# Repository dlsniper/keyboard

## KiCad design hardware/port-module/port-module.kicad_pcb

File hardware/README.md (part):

# hardware/

KiCad 10 projects for every board in the spec (§2a, §14). Generated by
`tools/gen_kicad.py`; checked by `tools/kicad-check.sh` (ERC + DRC on every
project, then `tools/check_interconnect.py`; reports in `build/kicad-check/`).

The generator always rewrites `lib/`, and only creates project files that are
missing, so schematic and board work is never overwritten.

## Rev 8 status (2026-09-26)

The spec moved to rev 8 (hub + dumb key modules, spec §17). **The files below are
still the rev 7 boards**, unchanged and committed as `0b22b91`; the board refactor is
the next step after the rev 8 docs are reviewed (`next.md`). Planned disposition:

| Project | Refs | Thickness | Rev 7 state | Rev 8 plan |
| --- | --- | --- | --- | --- |
| `keys-right/` `keys-left/` `keys-numpad/` | 1xx / 2xx / 3xx | 1.6 mm | empty | new design: sockets, LEDs, IS31FL3733, module controller (P19; `MSPM0G3505SPT`, link on PA0/PA1, PA18 `BSL_invoke` pull-down + rescue pad), LDO TPS7A0233PDBVR, `J_COMM` (order in spec §6, 2026-09-29), `J_DIAL` on `right` |
| `core/` | 4xx | 1.6 mm, 4 layers | schematic ERC 0; PCB 32 × 90 mm placed and routed except 7 nets (details below) | becomes **`hub-base/`**, one board (2026-09-29; the 2026-09-26 split into `hub-base/` + a vertical `hub-mcu/` board with `J_MCU` 2×30 is dropped): **MDBT50Q-U1MV2** (u.FL to the Yageo ANTX100P011B24003 PCB antenna in the case wall, 2026-10-01; the antenna needs ≥10 mm to copper, so a copper pull-back in the rear-left corner, size from M11), crystal, SWD, USB ESD, power path, TCA9548A, buttons, stacking headers; outline 94 × 77 mm (M11, front edge at y −30 behind the panel buttons); header centres chain (25, 20), slot (−5, 5), expansion (0, −20) mm from the board centre (x right from the keyboard, y to the rear), four M2 corner holes for the screws that join it to the connector layer (2026-09-29). The stock `RF_Module:Raytac_MDBT50Q` carries the antenna keepout zone, which the u.FL part does not need: whether to use a `keyboard:` copy without it is decided at capture. From `sch_core.py`: keep the power path, MCU support and expansion LDO in `sch_core.py`; drop the matrix, UART, link, module-ID and `J_ROW`/`J_COL`/`J_LED`/`J_LINK`/`J_BAT` parts; add the TCA9548A, the slot 2×16, chain 2×6 and expansion 2×10 headers (expansion pinout and CS0–CS3 with a 3V3 pull-up each per spec §6, X1), `PACK_EN`/`PACK_SENSE`, the `AUX_5V` OR input; new PCB, outline from the hub tower (M11) **Rev 8.1 (2026-09-30):** also takes the battery power path (spec §4): per pack input (`PACK_A`/`B`/`C`) SMF4L9.0CA + LM74610-Q1 + CSD17313Q2; CSD25402Q3A battery switch (TPS3840PL40 UVLO, `VDD` from the pack inputs via BAT54C + BAT54 since 2026-10-01, then 10 kΩ + 1 µF; battery sense on that node: 200 kΩ / 100 kΩ switched by a CSD25483F4 with a 470 kΩ gate pull-up and a third DMN63D8LDW half on `BAT_DIV_EN`; slide switch; DMN63D8LDW drivers; N2 pull-up 1 MΩ, Qb gate pull-up 1 MΩ, N1 pull-down 4.7 MΩ); LM74610 pump caps 1 µF; CSD25402Q3A USB switch (TPS3840PL43 on VBUS_IN; gate pull-up 10 kΩ; N4 gate delay 2.2 MΩ / 22 nF with a BAT54 bypass; VBUS_IN bleeder 100 kΩ; PL43 output also to a GPIO); `SYS` 100 µF effective; TPS630701 + XFL4020-152ME LED rail (`PS/SYNC` high, power save, 2026-10-01); TPS70933DBVR VSYS. Drops the TPS61099/MAX17222, TLV75733P, both TPS2116, TPS61023, TPS3840PH18 |
| `usb-port/` | 5xx | 1.6 mm | ERC 0 (2026-10-01) | keep as the host port board; **R502 OVLO 26.4 kΩ → 27.4 kΩ 0.1 % (E22, 2026-10-01)**: KTS1693 trip 5.38–5.78 V, under the MDBT50Q `VBUS` pad's 5.8 V abs-max |
| (new) `connector-wired/` | 12xx | 1.6 mm | — | wired connector layer carrier: slot 2×16 + chain 2×6 on top, chain pads underneath for the battery module's pogo pins, 12 Mill-Max 1578-0 gold target discs (2026-09-29, discs 2026-09-30; ESQ tails cut flush), chain/slot ESQ at the same centres as the core, 3 × `J_SLOT` (2026-09-26); slot header order in spec §6 (reversal-safe, slots 0/2 mirrored, 2026-09-29) |
| `link/` | 6xx | 1.6 mm | ERC 0, variants `upstream`/`downstream` | becomes **`comms/`** (hub population = the wired connector layer's socket boards): drop the KTS1693 population; variants `hub` (TPS22950L, `J_SLOT` 14) and `module` (BAT54C, `J_COMM` 10); VBUS TVS **TVS0500DRV** on both (was SMF6.0A; 2026-10-01, E7: stock symbol and WSON-6 footprint, land pattern checked against TI DRV0006A); CC1/CC2 in place of SBU; `J_SLOT`/`J_COMM` orders in spec §6 (2026-09-29), spares NC |
| `seam/` | 7xx | 1.2 mm | ERC 0, 4 variants | **retire** (seams are mechanical only); 7xx stays unused |
| `battery/` | 8xx | 1.6 mm | ERC 0 (rev 8 content) | **rev 8.1 (2026-09-30): becomes passive**: a 4×AA holder (MPD BC4AAPC at (−5, −15), cells along x; 2026-09-30), one PTC (Bourns MF-MSMF125/16X), the chain line shift (own pack → `PACK_A`; `PACK_A`/`PACK_B` from the discs → `PACK_B`/`PACK_C`; `PACK_C` ends), **pogo parts**: Samtec DW-06-17-T-D-254 riser at (25, 20) through a 1.6 mm cap board carrying the Mill-Max 827-22-012-10-004101 strip at (25, 28), 12 Mill-Max 1578-0 discs on ENIG pads underneath at (25, 28) (spec §4). The rev 7 pack chain, LM66200 and BAT54 leave the module (to the hub or dropped). The cap board is a small extra PCB per module |
| `dial/` | 9xx | 1.6 mm | ERC 0, PCB DRC + parity 0 | keep; recheck the A/B filter against the module controller (P19) |
| `expansion/` | 10xx | 1.6 mm | ERC 0 | keep, on the hub |
| `plate/plate-*` | none | 1.5 mm | outlines pending | keep |
| `common/` | — | — | empty sheets (LED matrix, link routing) | keep the LED matrix sheet; replace link routing with a module-controller block |

`tools/check_interconnect.py` needs its `MATES`/`PENDING` tables rebuilt for rev 8
(`J_SLOT`↔hub, `J_COMM`↔key boards, `J_CHAIN`).

## Projects (rev 7 detail, still describing the files on disk)

| Project | Refs | Thickness | Notes |
| --- | --- | --- | --- |
| `keys-right/` | 1xx | 1.6 mm | |
| `keys-left/` | 2xx | 1.6 mm | |
| `keys-numpad/` | 3xx | 1.6 mm | |
| `core/` | 4xx | 1.6 mm | **4 copper layers**, outline **32 × 90 mm** at (100, 100), placed 2026-09-16 (dielectric split is a placeholder until the fab stackup is chosen); antenna rule areas + net classes `VBUS_HI`/`POWER`/`USB` 2026-09-16; autorouted (Freerouting) 2026-09-16; rip-up 2026-09-24 (LED_BOOST hops to B.Cu at U410, R434 rotated 180°): 7 real + 8 on-purpose unconnected; `core.kicad_dru` U401 escape rule (0.127 mm inside `U401_ESCAPE`) 2026-09-25 |
| `usb-port/` | 5xx | 1.6 mm | min drill 0.15 mm (KTS1693 WLCSP) |
| `link/` | 6xx | 1.6 mm | min drill 0.15 mm (KTS1693 WLCSP) |
| `seam/` | 7xx | **1.2 mm** | SAMZO spring-half tails are 1.50 mm |
| `battery/` | 8xx | 1.6 mm | |
| `dial/` | 9xx | 1.6 mm | |
| `expansion/` | 10xx | 1.6 mm | 1xx–9xx were taken (2026-09-15) |
| `plate/plate-*` | none | 1.5 mm | FR4, no copper |

The core, battery, USB port, link, seam, dial and expansion schematics are written by `tools/sch_core.py`, `tools/sch_battery.py`,
`tools/sch_usb_port.py`, `tools/sch_link.py`, `tools/sch_seam.py`, `tools/sch_dial.py` and `tools/sch_expansion.py` (shared code in `tools/schlib.py`, kicad-sch-api in `.venv/`),
which refuse to overwrite a sheet that already has symbols unless run with `--force`,
and fail if KiCad's exported netlist differs from the nets they intended. Symbol UUIDs
are `uuid5("keyboard/<board>/<ref>")` (2026-09-15), so a `--force` rerun keeps PCB
footprints linked to their symbols. Mounting holes are schematic symbols
(`Mechanical:MountingHole`, not in BOM), so PCB schematic-parity reports nothing board-only.

`tools/check_interconnect.py` (2026-09-16) audits every JST GH header from the scripts'
`PARTS` tables: mated headers agree pin for pin through a per-pair net alias table
(`MATES`), with the same MPN; end-reversed, a power pin only faces its own net, and GND
facing a signal needs a `GND_SIGNAL_OK` reason; power nets have ≥2 contacts; pin counts
are unique per header type. Headers whose mate is on a keys-* board are listed in
`PENDING` until those schematics exist; an unlisted header is an error.

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
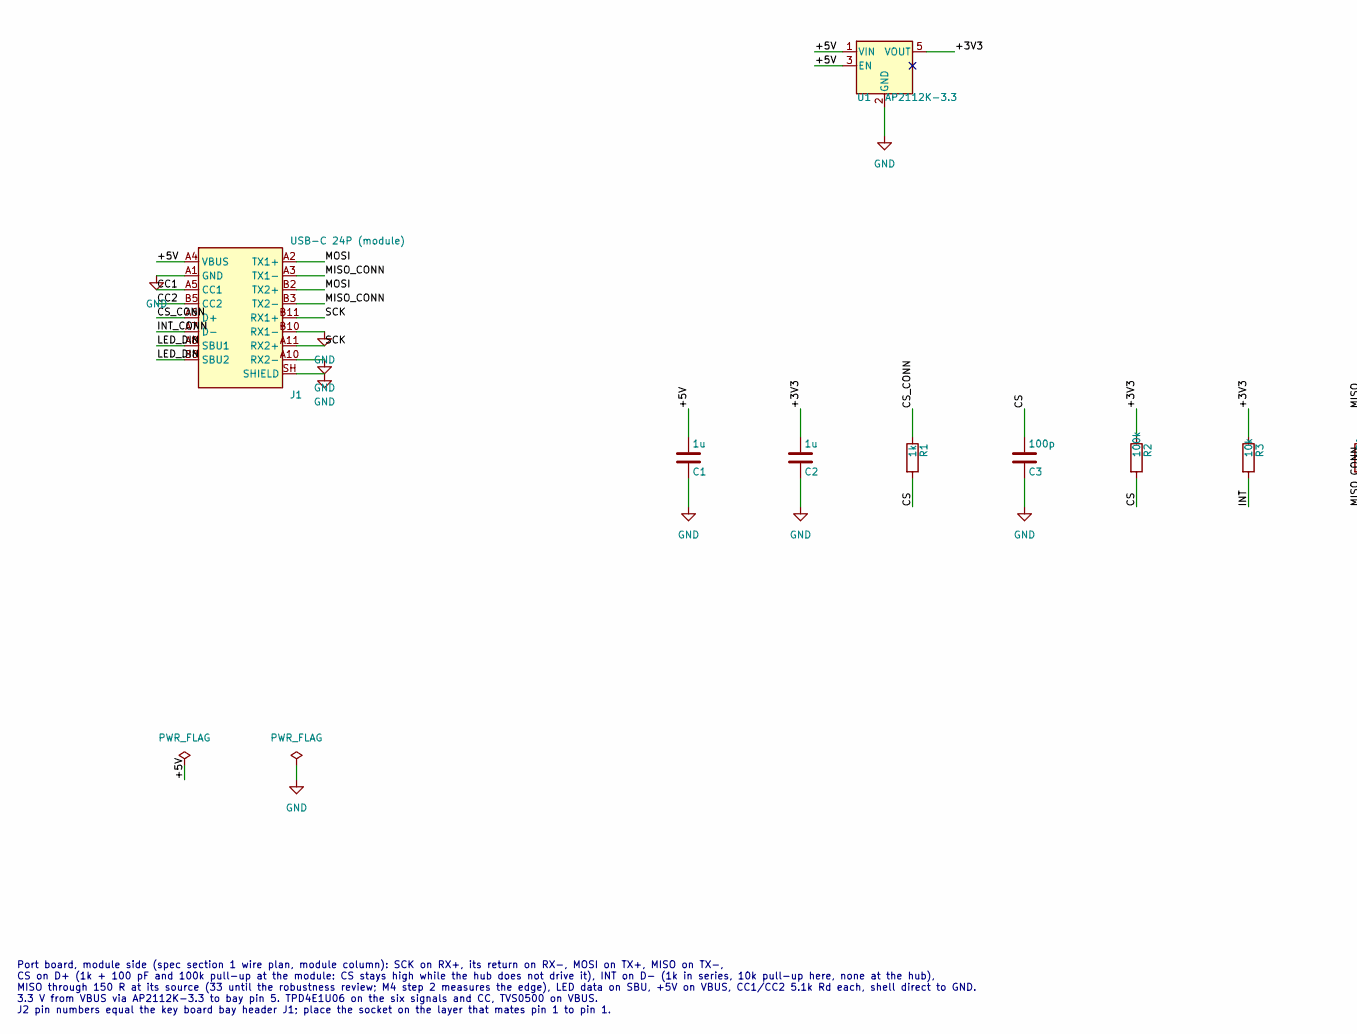
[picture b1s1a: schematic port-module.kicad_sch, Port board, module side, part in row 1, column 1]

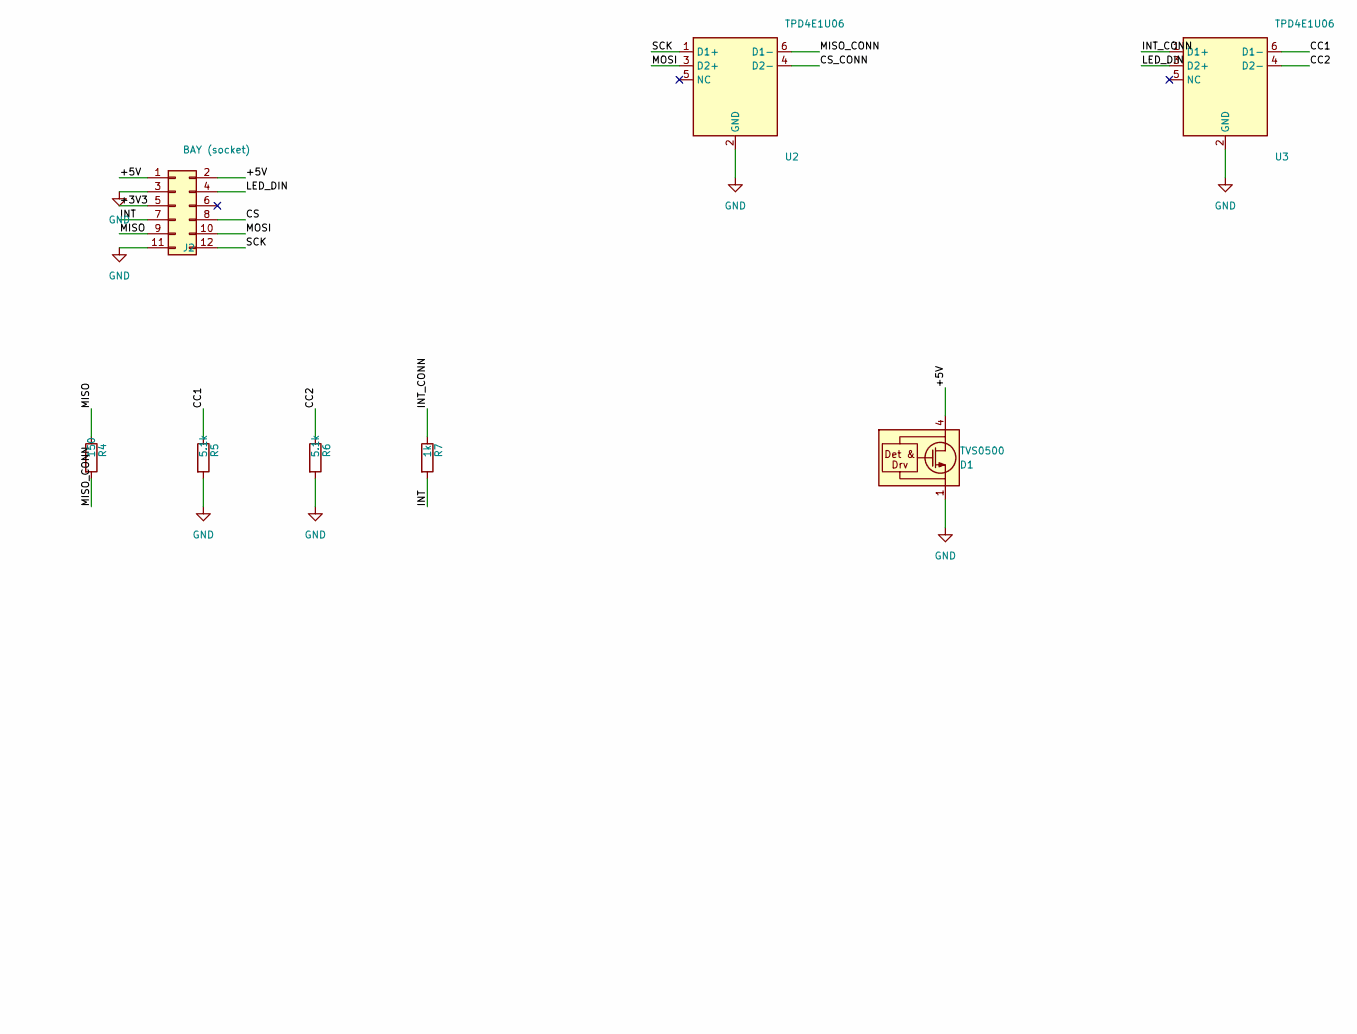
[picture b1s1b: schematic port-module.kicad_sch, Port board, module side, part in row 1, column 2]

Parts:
C1, C2: 1u; C_0805_2012Metric_Pad1.18x1.45mm_HandSolder; Voltage 16V
C3: 100p; C_0805_2012Metric_Pad1.18x1.45mm_HandSolder; Voltage 50V
D1: TVS0500; WSON-6-1EP_2x2mm_P0.65mm_EP1x1.6mm; MPN TI TVS0500DRVR
J1: USB-C 24P (module); USB_C_Receptacle_Amphenol_12401548E4-2A; MPN Amphenol 12401548E4-2A (24-pin, horizon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
J2: BAY (socket); PinSocket_2x06_P2.54mm_Vertical; MPN generic 2x6 2.54 mm socket
R1, R7: 1k; R_0805_2012Metric_Pad1.20x1.40mm_HandSolder; Tolerance 1%
R2: 100k; R_0805_2012Metric_Pad1.20x1.40mm_HandSolder; Tolerance 1%
R3: 10k; R_0805_2012Metric_Pad1.20x1.40mm_HandSolder; Tolerance 1%
R4: 150; R_0805_2012Metric_Pad1.20x1.40mm_HandSolder; Tolerance 1%
R5, R6: 5.1k; R_0805_2012Metric_Pad1.20x1.40mm_HandSolder; Tolerance 1%
U1: AP2112K-3.3; SOT-23-5; MPN Diodes Inc AP2112K-3.3TRG1
U2, U3: TPD4E1U06; TI_SOT-23-6_DBV0006A; MPN TI TPD4E1U06DBVR

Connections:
/+3V3: C2.1, J2.5, R2.1, R3.1, U1.5 (VOUT)
/+5V: C1.1, D1.4 (IN), D1.5 (IN), D1.6 (IN), J1.A4 (VBUS), J1.A9 (VBUS), J1.B4 (VBUS), J1.B9 (VBUS), J2.1, J2.2, U1.1 (VIN), U1.3 (EN)
/CC1: J1.A5 (CC1), R5.1, U3.6 (D1-)
/CC2: J1.B5 (CC2), R6.1, U3.4 (D2-)
/CS: C3.1, J2.8, R1.2, R2.2
/CS_CONN: J1.A6 (D+), J1.B6 (D+), R1.1, U2.4 (D2-)
/INT: J2.7, R3.2, R7.2
/INT_CONN: J1.A7 (D-), J1.B7 (D-), R7.1, U3.1 (D1+)
/LED_DIN: J1.A8 (SBU1), J1.B8 (SBU2), J2.4, U3.3 (D2+)
/MISO: J2.9, R4.1
/MISO_CONN: J1.A3 (TX1-), J1.B3 (TX2-), R4.2, U2.6 (D1-)
/MOSI: J1.A2 (TX1+), J1.B2 (TX2+), J2.10, U2.3 (D2+)
/SCK: J1.A11 (RX2+), J1.B11 (RX1+), J2.12, U2.1 (D1+)
GND: C1.2, C2.2, C3.2, D1.1 (GND), D1.2 (GND), D1.3 (GND), D1.7 (GND), J1.A1 (GND), J1.A10 (RX2-), J1.A12 (GND), J1.B1 (GND), J1.B10 (RX1-), J1.B12 (GND), J1.SH (SHIELD), J2.3, J2.11, R5.2, R6.2, U1.2 (GND), U2.2 (GND), U3.2 (GND)

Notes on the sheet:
Port board, module side (spec section 1 wire plan, module column): SCK on RX+, its return on RX-, MOSI on TX+, MISO on TX-, CS on D+ (1k + 100 pF and 100k pull-up at the module: CS stays high while the hub does not drive it), INT on D- (1k in series, 10k pull-up here, none at the hub), MISO through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

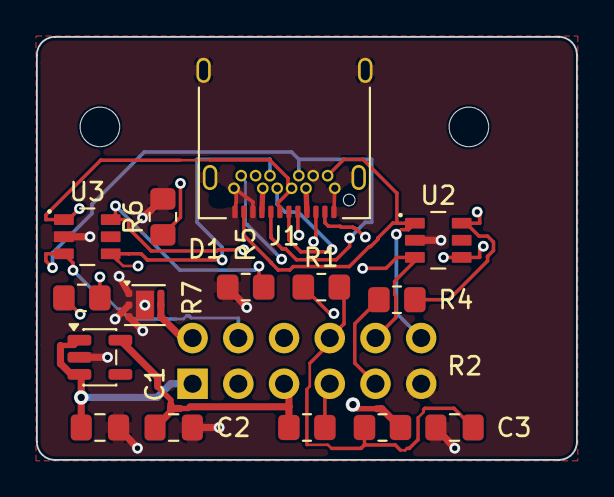
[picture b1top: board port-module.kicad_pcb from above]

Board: 4 copper layers, 30.0 x 23.5 mm, 18 parts (1 on the bottom side), 14 nets.

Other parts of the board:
H1, H2: MountingHole_2.2mm_M2

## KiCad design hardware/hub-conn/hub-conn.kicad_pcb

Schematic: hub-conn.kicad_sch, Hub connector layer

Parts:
C1, C5, C7, C9, C11, C13, C15, C26, C28, C34, C36, C37, C38, C46: 100n; C_0805_2012Metric_Pad1.18x1.45mm_HandSolder; Voltage 16V
C2, C3: 10n; C_0805_2012Metric_Pad1.18x1.45mm_HandSolder; Voltage 16V
C4, C6, C8, C10, C12, C14, C33: 10u; C_0805_2012Metric_Pad1.18x1.45mm_HandSolder; Voltage 16V
C16, C17, C18, C19, C20, C21, C22, C23, C24, C25: 1u; C_0805_2012Metric_Pad1.18x1.45mm_HandSolder; Voltage 16V
C27: 22n; C_0805_2012Metric_Pad1.18x1.45mm_HandSolder; Voltage 16V
C29, C30, C31, C32: 47u; C_1210_3225Metric_Pad1.33x2.70mm_HandSolder; Voltage 16V
C35, C47: 220u; CP_Elec_8x10; Voltage 16V; MPN 220 uF 16 V aluminium polymer, ESR 30 m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
C39, C43, C44, C45: 22u; C_1210_3225Metric_Pad1.33x2.70mm_HandSolder; Voltage 16V
C40: 1u; C_0603_1608Metric; Voltage 16V
C41: 15n; C_0805_2012Metric_Pad1.18x1.45mm_HandSolder; Voltage 16V
C42: 470p; C_0805_2012Metric_Pad1.18x1.45mm_HandSolder; Voltage 16V
D1, D2, D3: TVS0500; WSON-6-1EP_2x2mm_P0.65mm_EP1x1.6mm; MPN TI TVS0500DRVR
D4, D7, D10, D13, D15: SMF4L9.0CA; D_SOD-123FL_Littelfuse; MPN Littelfuse SMF4L9.0CA
D5, D8, D11, D14, D17, D18: BAT54C; SOT-23; MPN Diodes BAT54C-7-F
D6, D9, D12, D16, D19, D20: BAT54; SOT-23; MPN Diodes BAT54-7-F
D21: DNP (Qi); D_SOD-123F; MPN not fitted: Schottky SOD-123F, 20 V, ch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; not fitted
F1: DNP (Qi); Fuse_1206_3216Metric; MPN not fitted: chip fuse 1206, chosen with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; not fitted
J1: STACK (ESQ, socket up); PinSocket_2x25_P2.54mm_Vertical; MPN Samtec ESQ-125-24-T-D (stack-through: b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
J2: J_USB (host port board); JST_GH_SM11B-GHS-TB_1x11-1MP_P1.25mm_Horizontal; MPN JST SM11B-GHS-TB
J3: CHAIN (to AA module 1); PogoTarget_2x08_P2.54mm; MPN 16 x Mill-Max 1578-0-57-15-00-00-03-0 t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
J4: MODULE PORT A; USB_C_Receptacle_Amphenol_12401548E4-2A; MPN Amphenol 12401548E4-2A (24-pin, horizon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
J5: MODULE PORT B; USB_C_Receptacle_Amphenol_12401548E4-2A; MPN Amphenol 12401548E4-2A (24-pin, horizon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
J6: MODULE PORT C; USB_C_Receptacle_Amphenol_12401548E4-2A; MPN Amphenol 12401548E4-2A (24-pin, horizon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
L1: 4.7u; L_Coilcraft_XAL7070-XXX; MPN Coilcraft XAL7070-472ME (Isat 15 A, 14.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
Q1, Q4, Q7, Q10, Q13: SQ4184EY; SOIC-8_3.9x4.9mm_P1.27mm; MPN Vishay SQ4184EY-T1_GE3
Q2, Q5, Q8, Q11, Q18, Q20: CSD25402Q3A; VSON-8_3.3x3.3mm_P0.65mm_NexFET; MPN TI CSD25402Q3A
Q3, Q6, Q9, Q12, Q14, Q15, Q17, Q19, Q21: DMN63D8LDW; SOT-363_SC-70-6; MPN Diodes DMN63D8LDW-7
Q16: CSD25483F4; TI_PicoStar-3_1.0x0.6mm_YJC0003A; MPN TI CSD25483F4
R1, R13, R15, R16, R26, R28, R29, R39, R41, R42, R70, R81, R86: 10k; R_0805_2012Metric_Pad1.20x1.40mm_HandSolder; Tolerance 1%
R2, R3, R5, R6, R10, R11, R12, R17, R19, R23, R24, R25, R30, R32, R36, R37, R38, R43, R45, R49, R55, R61, R67, R73, R74, R80, R83, R88: 100k; R_0805_2012Metric_Pad1.20x1.40mm_HandSolder; Tolerance 1%
R4: 0R; R_0805_2012Metric_Pad1.20x1.40mm_HandSolder; Tolerance 1%; not fitted
R7, R8, R9, R20, R21, R22, R33, R34, R35: 33; R_0805_2012Metric_Pad1.20x1.40mm_HandSolder; Tolerance 1%
R14, R27, R40, R78: 1k; R_0805_2012Metric_Pad1.20x1.40mm_HandSolder; Tolerance 1%
R18, R31, R44: 330; R_0805_2012Metric_Pad1.20x1.40mm_HandSolder; Tolerance 1%
R46, R52, R58, R64, R75, R77: 1M; R_0805_2012Metric_Pad1.20x1.40mm_HandSolder; Tolerance 1%
R47, R53, R59, R65, R79: 2.2M; R_0805_2012Metric_Pad1.20x1.40mm_HandSolder; Tolerance 1%
R48, R54, R60, R66, R76: 4.7M; R_0805_2012Metric_Pad1.20x1.40mm_HandSolder; Tolerance 1%
R50, R56, R62, R68: 910k; R_0805_2012Metric_Pad1.20x1.40mm_HandSolder; Tolerance 1%
R51, R57, R63, R69: 22k; R_0805_2012Metric_Pad1.20x1.40mm_HandSolder; Tolerance 1%
R71: 470k; R_0805_2012Metric_Pad1.20x1.40mm_HandSolder; Tolerance 1%
R72: 200k; R_0805_2012Metric_Pad1.20x1.40mm_HandSolder; Tolerance 1%
R82: 15k; R_0805_2012Metric_Pad1.20x1.40mm_HandSolder; Tolerance 1%
R84: 54.9k; R_0805_2012Metric_Pad1.20x1.40mm_HandSolder; Tolerance 1%
R85: 133k; R_0805_2012Metric_Pad1.20x1.40mm_HandSolder; Tolerance 1%
R87: 49.9k; R_0805_2012Metric_Pad1.20x1.40mm_HandSolder; Tolerance 1%
R89: 31.6k; R_0805_2012Metric_Pad1.20x1.40mm_HandSolder; Tolerance 1%
R90: 12k; R_0805_2012Metric_Pad1.20x1.40mm_HandSolder; Tolerance 1%
U1: 74AHCT125; SOIC-14_3.9x8.7mm_P1.27mm; MPN 74AHCT125, SOIC-14
U2, U6, U10: TPS25810; Texas_RVC0020A_WQFN-20-1EP_3x4mm_P0.5mm_EP1.6x2.6mm; MPN TI TPS25810RVCR
U3, U7, U11: 74LVC125A; SOIC-14_3.9x8.7mm_P1.27mm; MPN 74LVC125A, SOIC-14
U4, U5, U8, U9, U12, U13: TPD4E1U06; TI_SOT-23-6_DBV0006A; MPN TI TPD4E1U06DBVR
U14, U16, U18, U20, U21: LM74610-Q1; VSSOP-8_3x3mm_P0.65mm; MPN TI LM74610QDGKRQ1
U15, U17, U19, U22: TPS3840PL43; TI_SOT-23-5_DBV0005A; MPN TI TPS3840PL43DBVR
U23: TPS3840PL40; TI_SOT-23-5_DBV0005A; MPN TI TPS3840PL40DBVR
U24: TPS3840PL36; TI_SOT-23-5_DBV0005A; MPN TI TPS3840PL36DBVR
U25: TPS552892; TI_VQFN-HR-21_5x3mm_RYQ0021A; MPN TI TPS552892RYQR
U26: TPS3700; TSOT-23-6; MPN TI TPS3700DDCR

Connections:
/+3V3: C7.1, C11.1, C15.1, J1.5, J1.6, Q14.2 (G1), Q14.5 (G2), Q15.2 (G1), Q15.5 (G2), R1.1, R2.1, R13.1, R15.1, R26.1, R28.1, R39.1, R41.1, U3.14 (VCC), U7.14 (VCC), U11.14 (VCC)
/+5V: C1.1, C4.1, C5.1, C8.1, C9.1, C12.1, C13.1, C43.1, C44.1, C45.1, C46.1, C47.1, J1.1, J1.2, R3.1, R85.1, R88.1, U1.13 (~4OE), U1.14 (VCC), U2.2 (IN1), U2.3 (IN1), U2.4 (IN2), U2.5 (AUX), U2.7 (CHG), U6.2 (IN1), U6.3 (IN1), U6.4 (IN2), U6.5 (AUX), U6.7 (CHG), U10.2 (IN1), U10.3 (IN1), U10.4 (IN2), U10.5 (AUX), U10.7 (CHG), U25.11 (VOUT), U25.12 (ISP), U25.13 (ISN)
/AUX_5V: F1.1, J3.8, J3.9
/AUX_F: D21.2 (A), F1.2
/BAT_DIV_EN: J1.39, Q17.2 (G1), R74.1
/BLD2: Q14.6 (D1), R51.2
/BLD3: Q14.3 (D2), R57.2
/BLD4: Q15.6 (D1), R63.2
/BLD5: Q15.3 (D2), R69.2
/BLK1: D14.3, Q12.2 (G1), R66.1
/BLK2: D5.3, D14.2, Q3.2 (G1), R48.1
/BLK3: D5.2, D8.3, Q6.2 (G1), R54.1
/BLK4: D8.2, D11.3, Q9.2 (G1), R60.1
/BOOT1: C37.1, U25.20 (BOOT1)
/BOOT2: C38.1, U25.19 (BOOT2)
/CC1: J2.3, R5.1
/CC1_A: J4.A5 (CC1), U2.11 (CC1), U5.6 (D1-)
/CC1_B: J5.A5 (CC1), U6.11 (CC1), U9.6 (D1-)
/CC1_C: J6.A5 (CC1), U10.11 (CC1), U13.6 (D1-)
/CC1_SENSE: C2.1, J1.35, R5.2
/CC2: J2.9, R6.1
/CC2_A: J4.B5 (CC2), U2.13 (CC2), U5.4 (D2-)
/CC2_B: J5.B5 (CC2), U6.13 (CC2), U9.4 (D2-)
/CC2_C: J6.B5 (CC2), U10.13 (CC2), U13.4 (D2-)
/CC2_SENSE: C3.1, J1.36, R6.2
/CHG_HI: R3.2, R4.1, U2.8 (CHG_HI), U6.8 (CHG_HI), U10.8 (CHG_HI)
/COMP: C42.1, R90.1, U25.15 (COMP)
/COMP_C: C41.1, R90.2
/CONV_EN: R83.2, R84.1, U25.1 (EN/UVLO), U26.6 (OUTB)
/CPH1: C22.1, U20.7 (VCAPH)
/CPH2: C16.1, U14.7 (VCAPH)
/CPH3: C18.1, U16.7 (VCAPH)
/CPH4: C20.1, U18.7 (VCAPH)
/CPH5: C23.1, U21.7 (VCAPH)
/CPL1: C22.2, U20.1 (VCAPL)
/CPL2: C16.2, U14.1 (VCAPL)
/CPL3: C18.2, U16.1 (VCAPL)
/CPL4: C20.2, U18.1 (VCAPL)
/CPL5: C23.2, U21.1 (VCAPL)
/CSB_A: R9.1, U3.8 (3Y)
/CSB_B: R22.1, U7.8 (3Y)
/CSB_C: R35.1, U11.8 (3Y)
/CSO_A: J4.A6 (D+), J4.B6 (D+), R9.2, U4.4 (D2-)
/CSO_B: J5.A6 (D+), J5.B6 (D+), R22.2, U8.4 (D2-)
/CSO_C: J6.A6 (D+), J6.B6 (D+), R35.2, U12.4 (D2-)
/CS_A: J1.15, R13.2, U3.1 (~1OE), U3.4 (~2OE), U3.9 (3A), U3.13 (~4OE)
/CS_B: J1.16, R26.2, U7.1 (~1OE), U7.4 (~2OE), U7.9 (3A), U7.13 (~4OE)
/CS_C: J1.17, R39.2, U11.1 (~1OE), U11.4 (~2OE), U11.9 (3A), U11.13 (~4OE)
/DET_A: J1.31, R15.2, U2.19 (~UFP), U3.10 (~3OE)
/DET_B: J1.32, R28.2, U6.19 (~UFP), U7.10 (~3OE)
/DET_C: J1.33, R41.2, U10.19 (~UFP), U11.10 (~3OE)
/DIV_G: Q16.1 (G), Q17.6 (D1), R71.2
/DIV_TOP: Q16.3 (D), R72.1
/EN_A: J1.27, R16.1, U2.6 (EN)
/EN_B: J1.28, R29.1, U6.6 (EN)
/EN_C: J1.29, R42.1, U10.6 (EN)
/FB: R88.2, R89.1, U25.14 (FB)
/FSW: R87.1, U25.6 (FSW)
/IDG1: Q10.4 (G), U20.2 (PULLDN), U20.6 (GATE)
/IDG2: Q1.4 (G), U14.2 (PULLDN), U14.6 (GATE)
/IDG3: Q4.4 (G), U16.2 (PULLDN), U16.6 (GATE)
/IDG4: Q7.4 (G), U18.2 (PULLDN), U18.6 (GATE)
/IDG5: Q13.4 (G), U21.2 (PULLDN), U21.6 (GATE)
/INTO_A: J4.A7 (D-), J4.B7 (D-), R14.1, U5.1 (D1+)
/INTO_B: J5.A7 (D-), J5.B7 (D-), R27.1, U9.1 (D1+)
/INTO_C: J6.A7 (D-), J6.B7 (D-), R40.1, U13.1 (D1+)
/INT_A: J1.19, R14.2
/INT_B: J1.20, R27.2
/INT_C: J1.21, R40.2
/L1: C37.2, L1.1, U25.8 (SW1)
/L2: C38.2, L1.2, U25.10 (SW2)
/LEDB_A: R18.1, U1.3 (1Y)
/LEDB_B: R31.1, U1.6 (2Y)
/LEDB_C: R44.1, U1.8 (3Y)
/LEDO_A: J4.A8 (SBU1), J4.B8 (SBU2), R18.2, U5.3 (D2+)
/LEDO_B: J5.A8 (SBU1), J5.B8 (SBU2), R31.2, U9.3 (D2+)
/LEDO_C: J6.A8 (SBU1), J6.B8 (SBU2), R44.2, U13.3 (D2+)
/LED_A: J1.23, R19.1, U1.2 (1A)
/LED_B: J1.24, R32.1, U1.5 (2A)
/LED_C: J1.25, R45.1, U1.9 (3A)
/MISO: J1.14, R2.2, U3.11 (4Y), U7.11 (4Y), U11.11 (4Y)
/MISO_A: J4.A10 (RX2-), J4.B10 (RX1-), R12.1, U3.12 (4A), U4.6 (D1-)
/MISO_B: J5.A10 (RX2-), J5.B10 (RX1-), R25.1, U7.12 (4A), U8.6 (D1-)
/MISO_C: J6.A10 (RX2-), J6.B10 (RX1-), R38.1, U11.12 (4A), U12.6 (D1-)
/MOSI: J1.13, U3.5 (2A), U7.5 (2A), U11.5 (2A)
/MOSIB_A: R8.1, U3.6 (2Y)
/MOSIB_B: R21.1, U7.6 (2Y)
/MOSIB_C: R34.1, U11.6 (2Y)
/MOSI_A: J4.A11 (RX2+), J4.B11 (RX1+), R8.2, R11.1, U4.3 (D2+)
/MOSI_B: J5.A11 (RX2+), J5.B11 (RX1+), R21.2, R24.1, U8.3 (D2+)
/MOSI_C: J6.A11 (RX2+), J6.B11 (RX1+), R34.2, R37.1, U12.3 (D2+)
/N12: Q19.1 (S1), Q19.3 (D2)
/NVBUS: Q19.5 (G2), Q21.6 (D1), R77.2
/OK2: D14.1, R50.2, U15.1 (~RESET)
/OK3: D5.1, R56.2, U17.1 (~RESET)
/OK4: D8.1, R62.2, U19.1 (~RESET)
/OK5: D11.1, D11.2, R68.2, U22.1 (~RESET)
/OV_SNS: R85.2, R86.1, U26.4 (INB-)
/PACK1: D13.1 (A1), D17.1, J3.1, J3.16, Q10.1 (S), Q10.2 (S), Q10.3 (S), U20.4 (ANODE)
/PACK2: D4.1 (A1), D17.2, J3.3, J3.14, Q1.1 (S), Q1.2 (S), Q1.3 (S), R49.1, R51.1, U14.4 (ANODE)
/PACK3: D7.1 (A1), D18.1, J3.4, J3.13, Q4.1 (S), Q4.2 (S), Q4.3 (S), R55.1, R57.1, U16.4 (ANODE)
/PACK4: D10.1 (A1), D18.2, J3.6, J3.11, Q7.1 (S), Q7.2 (S), Q7.3 (S), R61.1, R63.1, U18.4 (ANODE)
/PACK5: D15.1 (A1), D19.1 (A), J3.7, J3.10, Q13.1 (S), Q13.2 (S), Q13.3 (S), R67.1, R69.1, U21.4 (ANODE)
/PEN1: Q12.5 (G2), Q12.6 (D1), R65.2
/PEN2: Q3.5 (G2), Q3.6 (D1), R47.2
/PEN3: Q6.5 (G2), Q6.6 (D1), R53.2
/PEN4: Q9.5 (G2), Q9.6 (D1), R59.2
/PG1: Q11.4 (G), Q12.3 (D2), R64.2
/PG2: Q2.4 (G), Q3.3 (D2), R46.2
/PG3: Q5.4 (G), Q6.3 (D2), R52.2
/PG4: Q8.4 (G), Q9.3 (D2), R58.2
/PORT_FLT: J1.22, R1.2, U2.1 (~FAULT), U6.1 (~FAULT), U10.1 (~FAULT)
/PVDD2: C17.1, D6.3 (K), R49.2, R50.1, U15.2 (VDD)
/PVDD3: C19.1, D9.3 (K), R55.2, R56.1, U17.2 (VDD)
/PVDD4: C21.1, D12.3 (K), R61.2, R62.1, U19.2 (VDD)
/PVDD5: C24.1, D16.3 (K), R67.2, R68.1, U22.2 (VDD)
/PWR_SW_A: J1.41, U23.1 (~RESET)
/PWR_SW_B: J1.42, Q19.2 (G1), R76.1
/QB_G: Q18.4 (G), Q19.6 (D1), R75.2
/QU_G: Q20.4 (G), Q21.3 (D2), R78.2
/REFR_A: R17.2, U2.9 (REF_RTN)
/REFR_B: R30.2, U6.9 (REF_RTN)
/REFR_C: R43.2, U10.9 (REF_RTN)
/REF_A: R17.1, U2.10 (REF)
/REF_B: R30.1, U6.10 (REF)
/REF_C: R43.1, U10.10 (REF)
/SCK: J1.11, U3.2 (1A), U7.2 (1A), U11.2 (1A)
/SCKB_A: R7.1, U3.3 (1Y)
/SCKB_B: R20.1, U7.3 (1Y)
/SCKB_C: R33.1, U11.3 (1Y)
/SCK_A: J4.A2 (TX1+), J4.B2 (TX2+), R7.2, R10.1, U4.1 (D1+)
/SCK_B: J5.A2 (TX1+), J5.B2 (TX2+), R20.2, R23.1, U8.1 (D1+)
/SCK_C: J6.A2 (TX1+), J6.B2 (TX2+), R33.2, R36.1, U12.1 (D1+)
/SENSE_K: D17.3, D18.3, D19.3 (K), Q16.2 (S), R70.1, R71.1
/SYS: C29.1, C30.1, C31.1, C32.1, C33.1, C34.1, C35.1, C36.1, Q18.1 (D), Q18.2 (D), Q18.3 (D), Q20.5 (S), R78.1, R83.1, U25.7 (VIN), U26.5 (VDD)
/USB_DLY: C27.1, D20.1 (A), Q21.5 (G2), R79.2
/USB_DN: J1.9, J2.7
/USB_DP: J1.7, J2.5
/USB_OK: D20.3 (K), Q21.2 (G1), R79.1, R81.1, U24.1 (~RESET)
/USB_PRESENT: J1.30, R81.2, R82.1
/UVLO_VDD: C25.1, R70.2, U23.2 (VDD)
/VBAT: Q2.5 (S), Q5.5 (S), Q8.5 (S), Q11.5 (S), Q13.5 (D), Q13.6 (D), Q13.7 (D), Q13.8 (D), Q18.5 (S), R46.1, R47.1, R52.1, R53.1, R58.1, R59.1, R64.1, R65.1, R75.1, R77.1, U21.8 (CATHODE)
/VBAT_SENSE: C26.1, J1.37, R72.2, R73.1
/VBUS_A: C6.1, D1.4 (IN), D1.5 (IN), D1.6 (IN), J4.A4 (VBUS), J4.A9 (VBUS), J4.B4 (VBUS), J4.B9 (VBUS), U2.14 (OUT), U2.15 (OUT)
/VBUS_B: C10.1, D2.4 (IN), D2.5 (IN), D2.6 (IN), J5.A4 (VBUS), J5.A9 (VBUS), J5.B4 (VBUS), J5.B9 (VBUS), U6.14 (OUT), U6.15 (OUT)
/VBUS_C: C14.1, D3.4 (IN), D3.5 (IN), D3.6 (IN), J6.A4 (VBUS), J6.A9 (VBUS), J6.B4 (VBUS), J6.B9 (VBUS), U10.14 (OUT), U10.15 (OUT)
/VBUS_IN: C28.1, D21.1 (K), J2.1, J2.6, J2.11, Q20.1 (D), Q20.2 (D), Q20.3 (D), R80.1, U24.2 (VDD)
/VCC5: C39.1, C40.1, U25.18 (VCC)
/VM1: Q10.5 (D), Q10.6 (D), Q10.7 (D), Q10.8 (D), Q11.1 (D), Q11.2 (D), Q11.3 (D), U20.8 (CATHODE)
/VM2: Q1.5 (D), Q1.6 (D), Q1.7 (D), Q1.8 (D), Q2.1 (D), Q2.2 (D), Q2.3 (D), U14.8 (CATHODE)
/VM3: Q4.5 (D), Q4.6 (D), Q4.7 (D), Q4.8 (D), Q5.1 (D), Q5.2 (D), Q5.3 (D), U16.8 (CATHODE)
/VM4: Q7.5 (D), Q7.6 (D), Q7.7 (D), Q7.8 (D), Q8.1 (D), Q8.2 (D), Q8.3 (D), U18.8 (CATHODE)
GND: C1.2, C2.2, C3.2, C4.2, C5.2, C6.2, C7.2, C8.2, C9.2, C10.2, C11.2, C12.2, C13.2, C14.2, C15.2, C17.2, C19.2, C21.2, C24.2, C25.2, C26.2, C27.2, C28.2, C29.2, C30.2, C31.2, C32.2, C33.2, C34.2, C35.2, C36.2, C39.2, C40.2, C41.2, C42.2, C43.2, C44.2, C45.2, C46.2, C47.2, D1.1 (GND), D1.2 (GND), D1.3 (GND), D1.7 (GND), D2.1 (GND), D2.2 (GND), D2.3 (GND), D2.7 (GND), D3.1 (GND), D3.2 (GND), D3.3 (GND), D3.7 (GND), D4.2 (A2), D6.1 (A), D7.2 (A2), D9.1 (A), D10.2 (A2), D12.1 (A), D13.2 (A2), D15.2 (A2), D16.1 (A), J1.3, J1.4, J1.8, J1.10, J1.12, J1.18, J1.26, J1.34, J1.38, J1.49, J1.50, J2.2, J2.4, J2.10, J3.2, J3.5, J3.12, J3.15, J4.A1 (GND), J4.A3 (TX1-), J4.A12 (GND), J4.B1 (GND), J4.B3 (TX2-), J4.B12 (GND), J4.SH (SHIELD), J5.A1 (GND), J5.A3 (TX1-), J5.A12 (GND), J5.B1 (GND), J5.B3 (TX2-), J5.B12 (GND), J5.SH (SHIELD), J6.A1 (GND), J6.A3 (TX1-), J6.A12 (GND), J6.B1 (GND), J6.B3 (TX2-), J6.B12 (GND), J6.SH (SHIELD), Q3.1 (S1), Q3.4 (S2), Q6.1 (S1), Q6.4 (S2), Q9.1 (S1), Q9.4 (S2), Q12.1 (S1), Q12.4 (S2), Q14.1 (S1), Q14.4 (S2), Q15.1 (S1), Q15.4 (S2), Q17.1 (S1), Q17.3 (D2), Q17.4 (S2), Q17.5 (G2), Q19.4 (S2), Q21.1 (S1), Q21.4 (S2), R4.2, R10.2, R11.2, R12.2, R16.2, R19.2, R23.2, R24.2, R25.2, R29.2, R32.2, R36.2, R37.2, R38.2, R42.2, R45.2, R48.2, R54.2, R60.2, R66.2, R73.2, R74.2, R76.2, R80.2, R82.2, R84.2, R86.2, R87.2, R89.2, U1.1 (~1OE), U1.4 (~2OE), U1.7 (GND), U1.10 (~3OE), U1.12 (4A), U2.12 (GND), U2.21 (GND), U3.7 (GND), U4.2 (GND), U5.2 (GND), U6.12 (GND), U6.21 (GND), U7.7 (GND), U8.2 (GND), U9.2 (GND), U10.12 (GND), U10.21 (GND), U11.7 (GND), U12.2 (GND), U13.2 (GND), U15.3 (GND), U17.3 (GND), U19.3 (GND), U22.3 (GND), U23.3 (GND), U24.3 (GND), U25.2 (MODE), U25.5 (DITH/SYNC), U25.9 (PGND), U25.17 (AGND), U26.2 (GND), U26.3 (INA+)

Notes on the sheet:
Hub connector layer (spec sections 1, 3, 3a). J1 = frozen stack connector to the core layer; +3V3 comes from the Pico. Module ports A-C: hub column of the wire plan (SCK on TX+, its return on TX-, MOSI on RX+, MISO on RX-, CS on D+, INT on D-, LED data on SBU). TPS25810 per port: CHG high, CHG_HI 1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

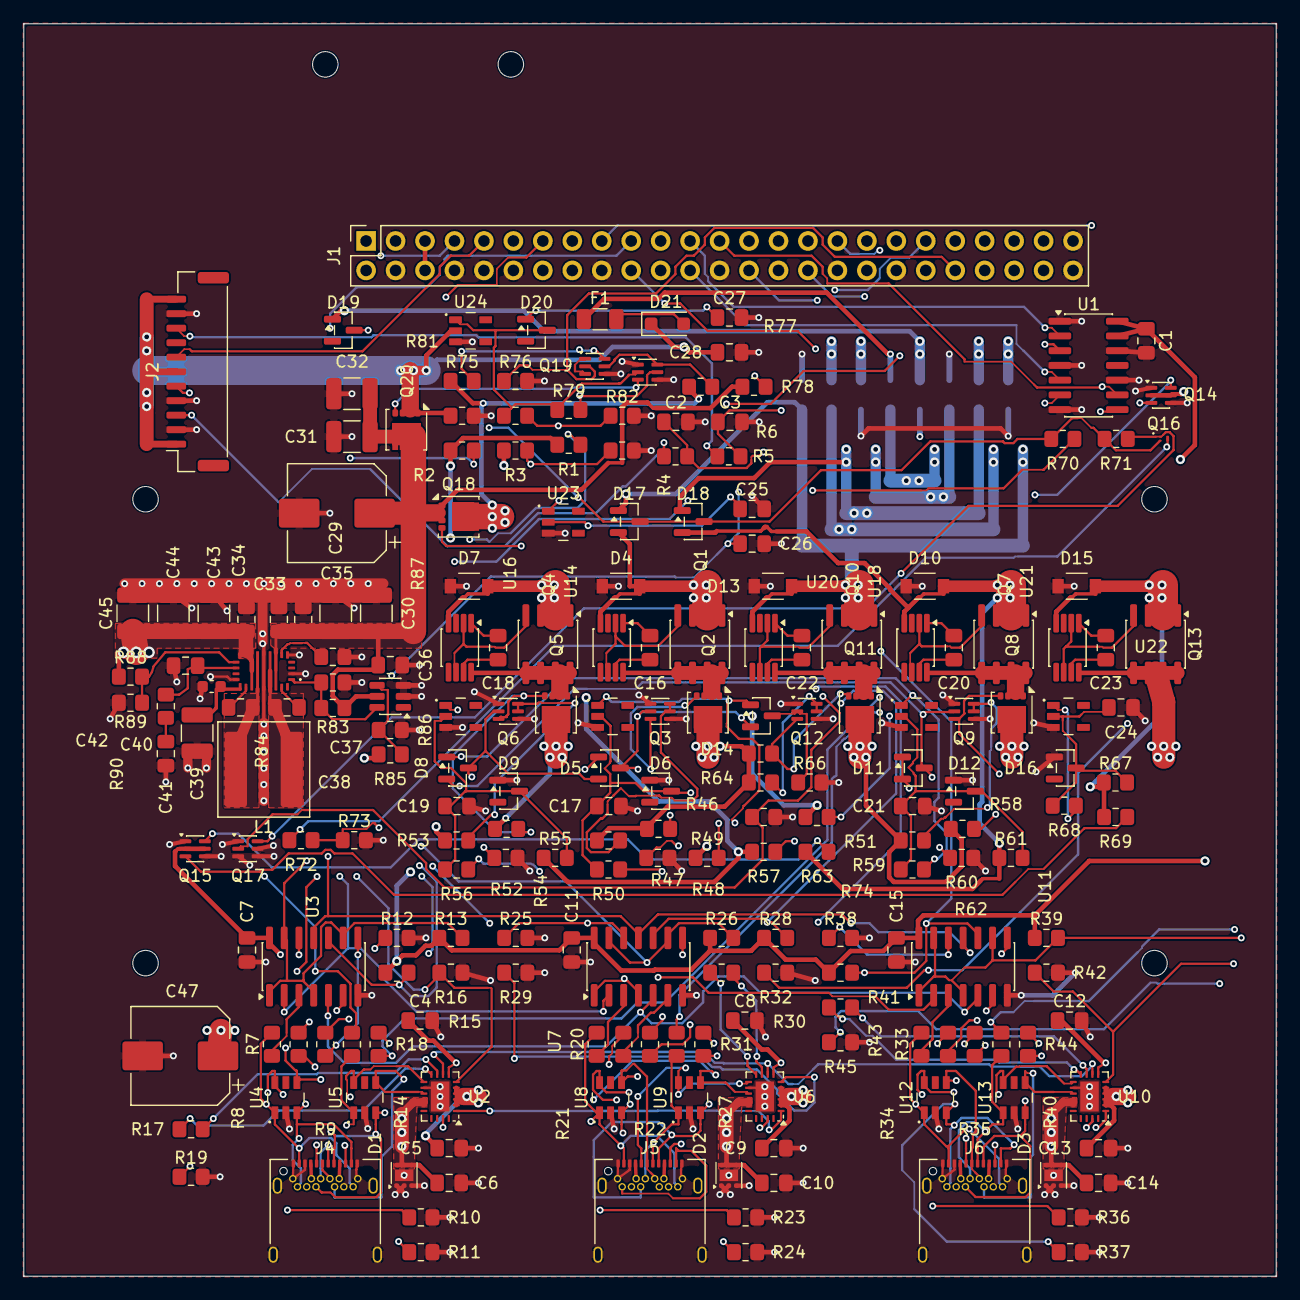
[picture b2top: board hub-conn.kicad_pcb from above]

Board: 4 copper layers, 108.0 x 108.0 mm, 219 parts (1 on the bottom side), 153 nets.

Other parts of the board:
H1, H2, H3, H4, H5, H6: MountingHole_2.2mm_M2

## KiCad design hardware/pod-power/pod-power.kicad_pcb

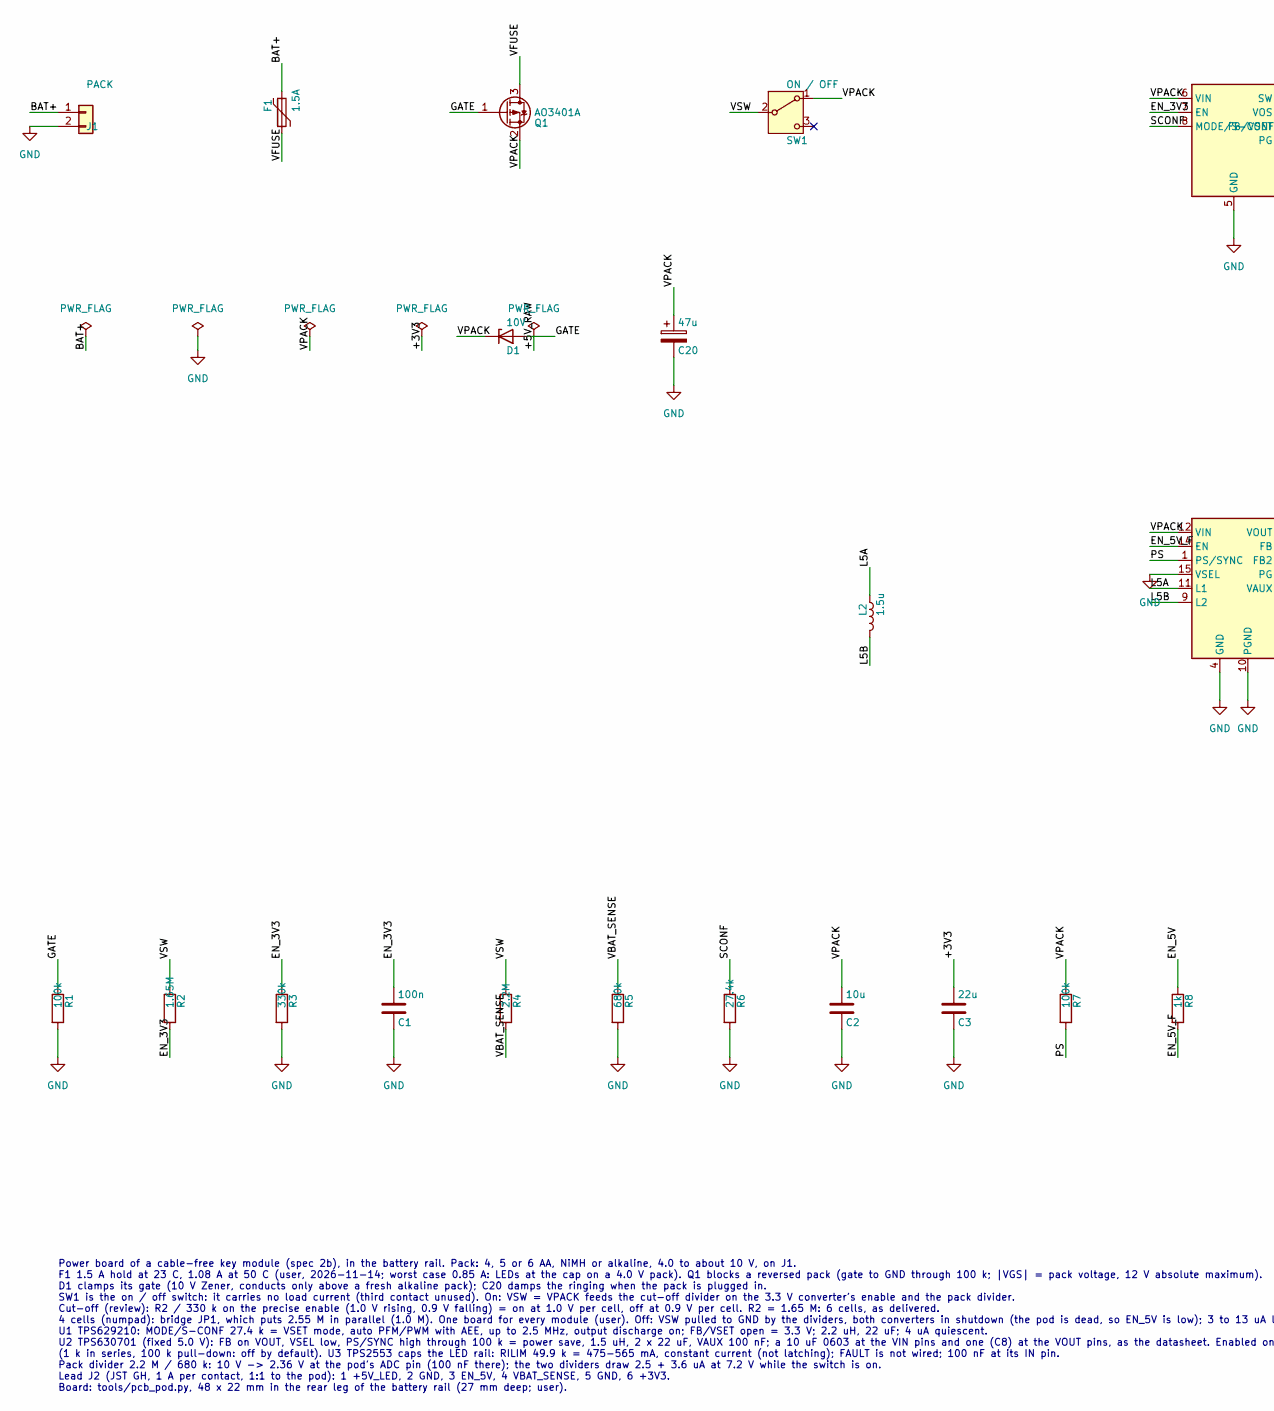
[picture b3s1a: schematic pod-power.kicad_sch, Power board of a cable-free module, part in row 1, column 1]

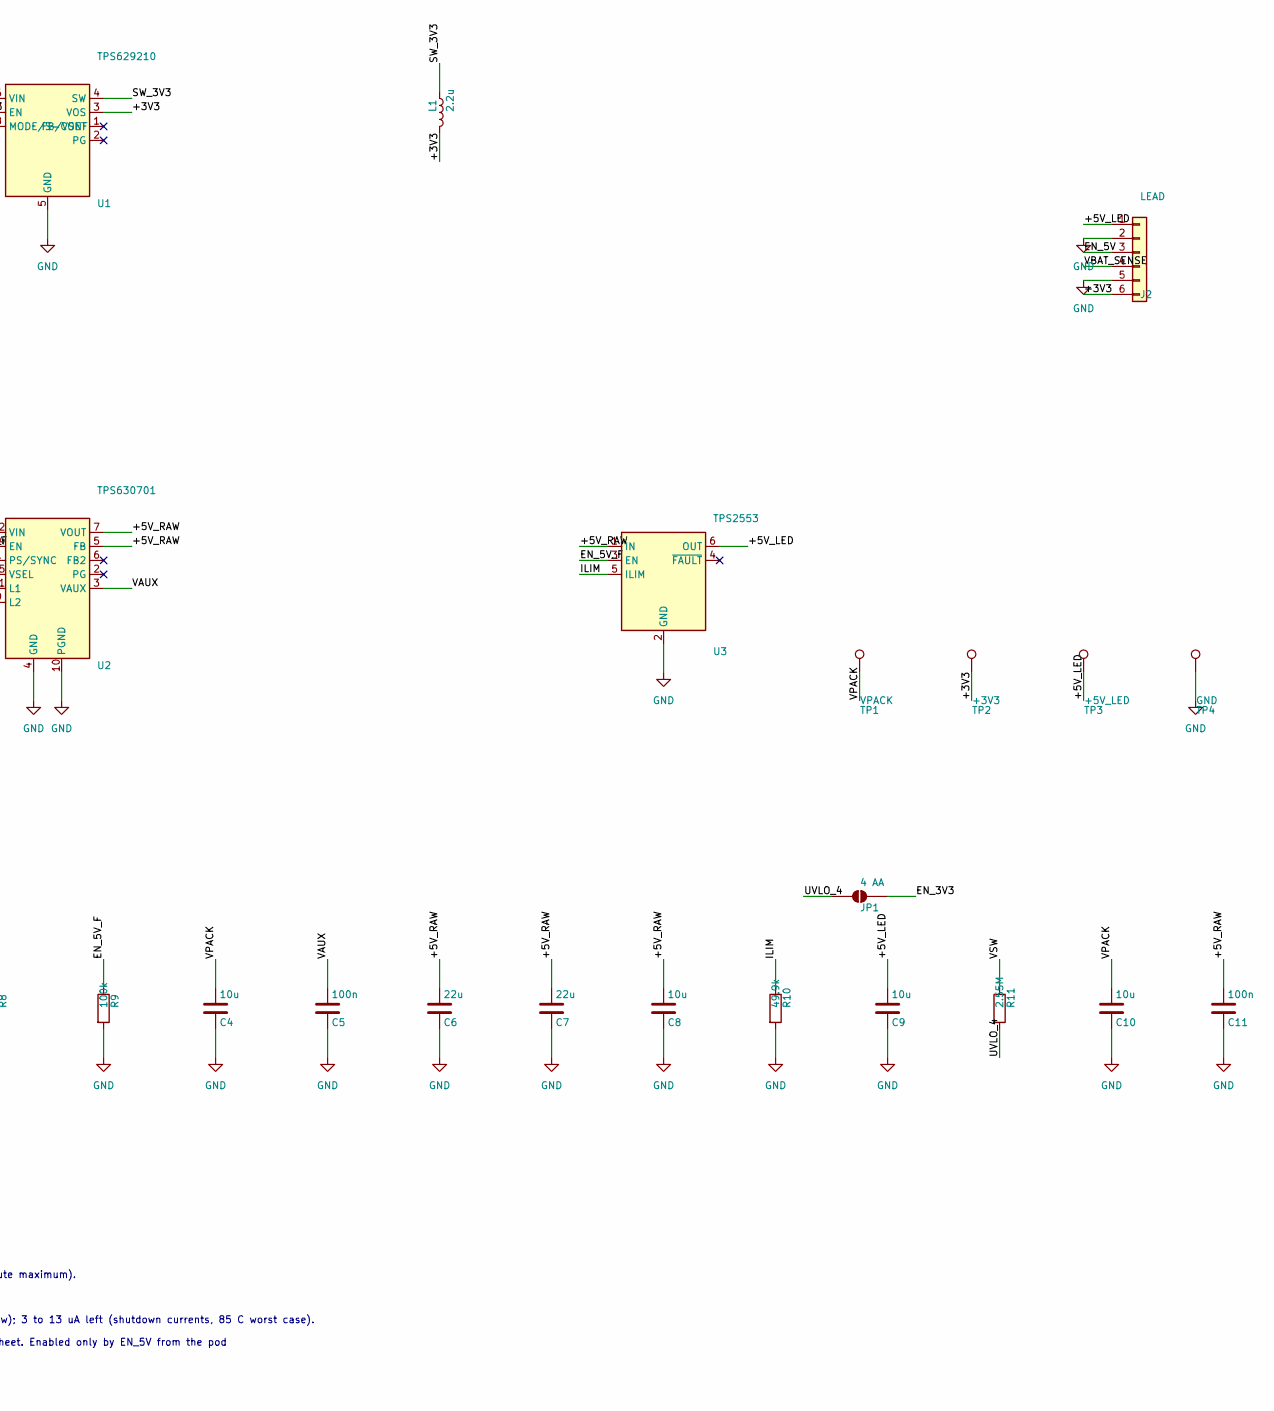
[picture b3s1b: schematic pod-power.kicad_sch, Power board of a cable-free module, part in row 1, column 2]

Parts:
C1, C5, C11: 100n; C_0603_1608Metric; Voltage 16V
C2, C4: 10u; C_1206_3216Metric; Voltage 25V
C3: 22u; C_1206_3216Metric; Voltage 10V
C6, C7: 22u; C_1206_3216Metric; Voltage 16V
C8: 10u; C_0603_1608Metric; Voltage 16V
C9: 10u; C_0805_2012Metric; Voltage 16V
C10: 10u; C_0603_1608Metric; Voltage 25V
C20: 47u; CP_Elec_6.3x5.8; Voltage 25V; MPN polymer or electrolytic, 6.3 mm can
D1: 10V; D_SOD-123; MPN BZT52C10 class
F1: 1.5A; Fuse_1812_4532Metric; MPN Bourns MF-MSMF150/16X (hold 1.5 A at 23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
J1: PACK; JST_XH_S2B-XH-A_1x02_P2.50mm_Horizontal; MPN JST S2B-XH-A (3 A per contact)
J2: LEAD; JST_GH_BM06B-GHS-TBT_1x06-1MP_P1.25mm_Vertical; MPN JST BM06B-GHS-TBT (vertical: the lead i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
JP1: 4 AA; SolderJumper-2_P1.3mm_Open_RoundedPad1.0x1.5mm
L1: 2.2u; L_Coilcraft_XGL3530; MPN Coilcraft XGL3530-222ME
L2: 1.5u; L_Coilcraft_XFL4020; MPN Coilcraft XFL4020-152ME
Q1: AO3401A; SOT-23; MPN Alpha & Omega AO3401A
R1, R7, R9: 100k; R_0603_1608Metric; Tolerance 1%
R2: 1.65M; R_0603_1608Metric; Tolerance 1%
R3: 330k; R_0603_1608Metric; Tolerance 1%
R4: 2.2M; R_0603_1608Metric; Tolerance 1%
R5: 680k; R_0603_1608Metric; Tolerance 1%
R6: 27.4k; R_0603_1608Metric; Tolerance 1%
R8: 1k; R_0603_1608Metric; Tolerance 1%
R10: 49.9k; R_0603_1608Metric; Tolerance 1%
R11: 2.55M; R_0603_1608Metric; Tolerance 1%
SW1: ON / OFF; SW_Slide_SPDT_Angled_CK_OS102011MA1Q; MPN C&K OS102011MA1QN1 (common = pin 2)
TP1: VPACK; TestPoint_Pad_D1.5mm
TP2: +3V3; TestPoint_Pad_D1.5mm
TP3: +5V_LED; TestPoint_Pad_D1.5mm
TP4: GND; TestPoint_Pad_D1.5mm
U1: TPS629210; SOT-583-8; MPN TI TPS629210DRLR
U2: TPS630701; TI_VQFN-HR-15_2.5x3mm_RNM0015A; MPN TI TPS630701RNMR
U3: TPS2553; TI_SOT-23-6_DBV0006A; MPN TI TPS2553DBVR

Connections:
/+3V3: C3.1, J2.6, L1.2, TP2.1, U1.3 (VOS)
/+5V_LED: C9.1, J2.1, TP3.1, U3.6 (OUT)
/+5V_RAW: C6.1, C7.1, C8.1, C11.1, U2.5 (FB), U2.7 (VOUT), U2.8 (VOUT), U3.1 (IN)
/BAT+: F1.1, J1.1
/EN_3V3: C1.1, JP1.2 (B), R2.2, R3.1, U1.7 (EN)
/EN_5V: J2.3, R8.1
/EN_5V_F: R8.2, R9.1, U2.14 (EN), U3.3 (EN)
/GATE: D1.2 (A), Q1.1 (G), R1.1
/ILIM: R10.1, U3.5 (ILIM)
/L5A: L2.1, U2.11 (L1)
/L5B: L2.2, U2.9 (L2)
/PS: R7.2, U2.1 (PS/SYNC)
/SCONF: R6.1, U1.8 (MODE/S-CONF)
/SW_3V3: L1.1, U1.4 (SW)
/UVLO_4: JP1.1 (A), R11.2
/VAUX: C5.1, U2.3 (VAUX)
/VBAT_SENSE: J2.4, R4.2, R5.1
/VFUSE: F1.2, Q1.3 (D)
/VPACK: C2.1, C4.1, C10.1, C20.1, D1.1 (K), Q1.2 (S), R7.1, SW1.1 (A), TP1.1, U1.6 (VIN), U2.12 (VIN), U2.13 (VIN)
/VSW: R2.1, R4.1, R11.1, SW1.2 (B)
GND: C1.2, C2.2, C3.2, C4.2, C5.2, C6.2, C7.2, C8.2, C9.2, C10.2, C11.2, C20.2, J1.2, J2.2, J2.5, R1.2, R3.2, R5.2, R6.2, R9.2, R10.2, TP4.1, U1.5 (GND), U2.4 (GND), U2.10 (PGND), U2.15 (VSEL), U3.2 (GND)

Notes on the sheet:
Power board of a cable-free key module (spec 2b), in the battery rail. Pack: 4, 5 or 6 AA, NiMH or alkaline, 4.0 to about 10 V, on J1. F1 1.5 A hold at 23 C, 1.08 A at 50 C (user, 2026-11-14; worst case 0.85 A: LEDs at the cap on a 4.0 V pack). Q1 blocks a reversed pack (gate to GND through 100 k; 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

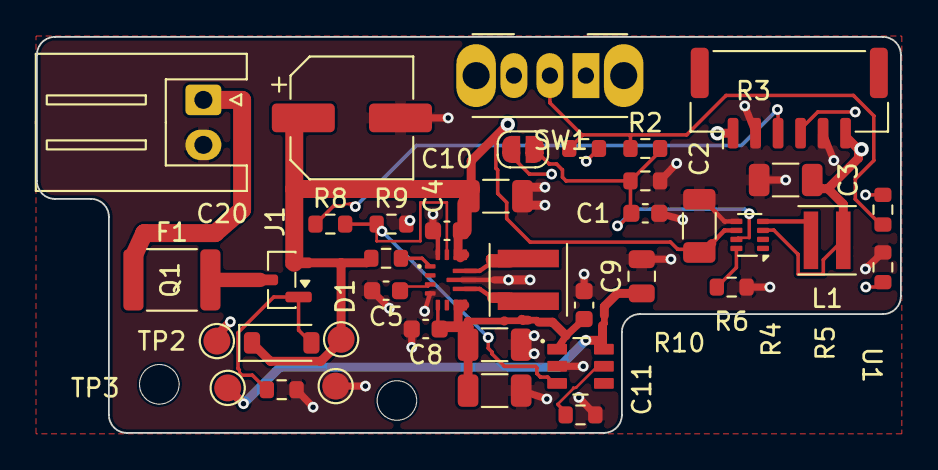
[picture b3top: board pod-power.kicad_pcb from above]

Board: 4 copper layers, 48.0 x 22.0 mm, 41 parts (0 on the bottom side), 21 nets.

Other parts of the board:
H1, H2: MountingHole_2.2mm_M2

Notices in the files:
hardware/README.md:
A subset of [kiswitch](https://github.com/kiswitch/kiswitch) (MIT / CC-BY-SA 4.0),
